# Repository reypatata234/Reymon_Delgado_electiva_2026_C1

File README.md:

# Reymon_Delgado_electiva_2026_C1
repositorio para subir informes y tareas  de la materia de electiva.

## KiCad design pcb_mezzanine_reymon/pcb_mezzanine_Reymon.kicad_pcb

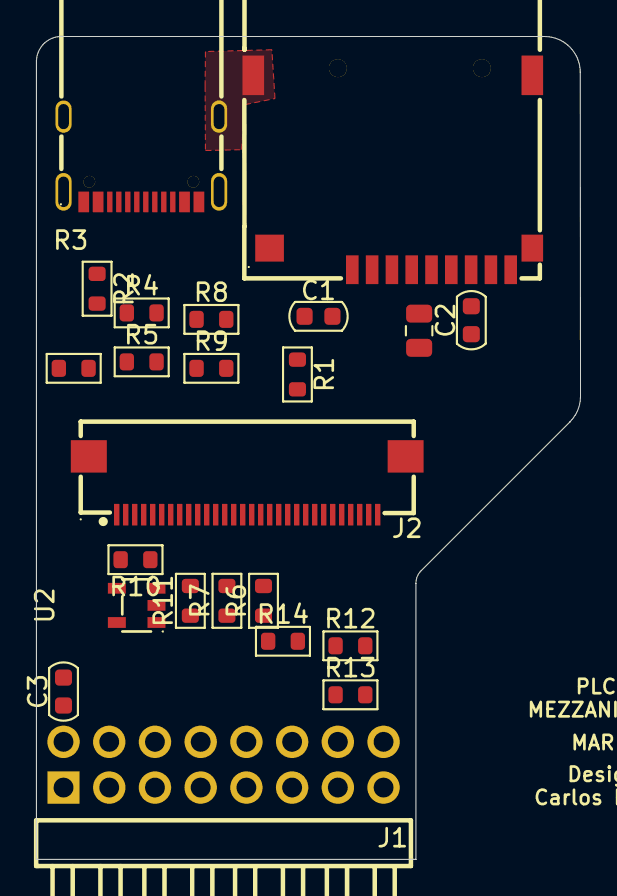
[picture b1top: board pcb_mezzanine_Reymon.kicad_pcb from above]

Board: 4 copper layers, 30.2 x 45.7 mm, 23 parts (0 on the bottom side), 27 nets, no tracks yet.

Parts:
C1: 47uF; C_0603_1608Metric
C2: 100nF; C_0603_1608Metric
C3: 10uF; C_0603_1608Metric
Card1: TF-115; TF-SMD_TF-115
J1: PZ254R-12-16P; HDR-TH_16P-P2.54-H-M-R2-C8-S2.54
J2: FPC-05FB-30PH20; FPC-SMD_30P-P0.50_FPC-05FB-30PH20
L1: 600 Ohm; C_0805_2012Metric
R1, R2: 5.1k; R_0603_1608Metric
R3, R5: 2.2K; R_0603_1608Metric
R4, R8, R9, R12, R13, R14: 10K; R_0603_1608Metric
R6: 10R; R_0603_1608Metric
R7: 220R; R_0603_1608Metric
R10: 6.8K; R_0603_1608Metric
R11: 300; R_0603_1608Metric
U1: MC-121-L119; USB-C-SMD_HANBO_MC-121-L119
U2: MT9700-N; SOT-23-5_L2.9-W1.6-P0.95-LS2.9-BL

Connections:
+3.3V: C3.1, J1.2, L1.2, R3.1, R4.1, R5.1, R8.1, R9.1, R12.1, R13.1, R14.1, U2.5 (VIN)
+5V: J1.1, U1.A4B9 (VBUS), U1.B4A9 (VBUS)
/I2C_SCK: J1.10, J2.26
/I2C_SDA: J1.8, J2.27
/IM1: J2.4, R13.2
/IM2: J2.3, R12.2
/LCD_CS: J1.13, J2.6
/LCD_EN: J1.12, U2.4 (EN)
/LED+: J2.20, R11.2
/RESET: J1.11, J2.5, J2.29, R14.2
/SD_CS: Card1.2 (CD/DAT3), J1.3, R9.2
/SPI_CLK: J1.9, J2.7, R6.1
/SPI_MISO: J1.7, J2.8, R5.2, R7.1
/SPI_MOSI: Card1.3 (CMD), J1.5, J2.10, R3.2
/TP_INT: J1.14, J2.28
/USB+: J1.4, U1.A6 (DP1), U1.B6 (DP2)
/USB-: J1.6, U1.A7 (DN1), U1.B7 (DN2)
GND: C1.2, C2.2, C3.2, Card1.6 (VSS), Card1.10 (SHELL), Card1.11 (SHELL), Card1.12 (SHELL), Card1.13 (SHELL), J1.15, J1.16, J2.1, J2.21, J2.22, J2.23, J2.24, J2.30, J2.31, J2.32, R1.2, R2.2, R10.2, U1.13 (EH), U1.A1B12 (GND), U1.B1A12 (GND), U2.2 (GND)
unnamed: Card1.5 (CLK), R6.2
unnamed: Card1.7 (DAT0), R7.2
unnamed: Card1.8 (DAT1), R4.2
unnamed: Card1.1 (DAT2), R8.2
unnamed: C1.1, C2.1, Card1.4 (VDD), L1.1
unnamed: R1.1, U1.A5 (CC1)
unnamed: R2.1, U1.B5 (CC2)
unnamed: R10.1, U2.3 (SET)
VDD: J2.2, J2.25, R11.1, U2.1 (VOUT)

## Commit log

2026-01-25 Update README to clarify project purpose
2026-02-12 plc case tapa de arriba y abajo v1
2026-03-12 primera version de la plantilla y resumen mbse completo
2026-03-12 version 1 circuito investigados
2026-03-22 agrego gitignore para ignorar fcbak, archivo de recuperacion
2026-03-22 cambios en parte de abajo plc
2026-03-22 anadir ,pcb, mezzazine,subemsamblaje de tapa inferior con pcb plc, ensamblaje con subensamblaje anadiendo mezzanine: aun en trabajo
2026-03-22 anadido de git ignore actualizado y bien hecho
2026-03-22 arreglado todo respecto a lo FCBak
2026-03-23 ensamblaje plc,con mezzanine ajustada en tamano y coindente con la cara de arriba de tapa superior, arreglo de tamano de extrusion de tapa superior, hecho sketch que marca en donde iran los agujeros 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
2026-03-23 fotos de circuitos investigado, diagramas de bloque de estos circuitos<aun en proceso>,se anadio zip y lck al gitignore, y subir pcb_mezzanine con ajuste de tamano y plano de tierra<aun en proceso de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
